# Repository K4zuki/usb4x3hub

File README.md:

# C92で購入いただいた方へ
- この本のPDFファイルは
  [こちら](https://github.com/K4zuki/usb4x3hub/releases/tag/c92-print-out)
- この本に登場する基板のデータは
  [こちら](https://github.com/K4zuki/usb4x3hub/releases/tag/r0.5-gerber-out)
- 秋月メモリ液晶基板の本は[こちら](https://github.com/K4zuki/AkiSpiLcd)です

# このリポジトリは何
コミケ９２に向けて書いていた本の原稿と、同時頒布を目指して設計を進めていた
基板の設計データです。原稿はmarkdownで書かれています。 設計データは
Eagle７系のbrdファイルとガーバデータです。

# USB4x3HUB: connects 4 USB hosts to share 3-port USB HUB
If you have **PCs, MACs, LINUXes, XBOXes and/or PS4s**, you can share your favorite Keyboard and Mouse (and one more)

> NOTE: I do not have PS4 so it is not tested;USB4x3HUB might not work with PS4

**rev 0.5 - みんなのラボ brand**

<!-- 
**rev 0.1** -->

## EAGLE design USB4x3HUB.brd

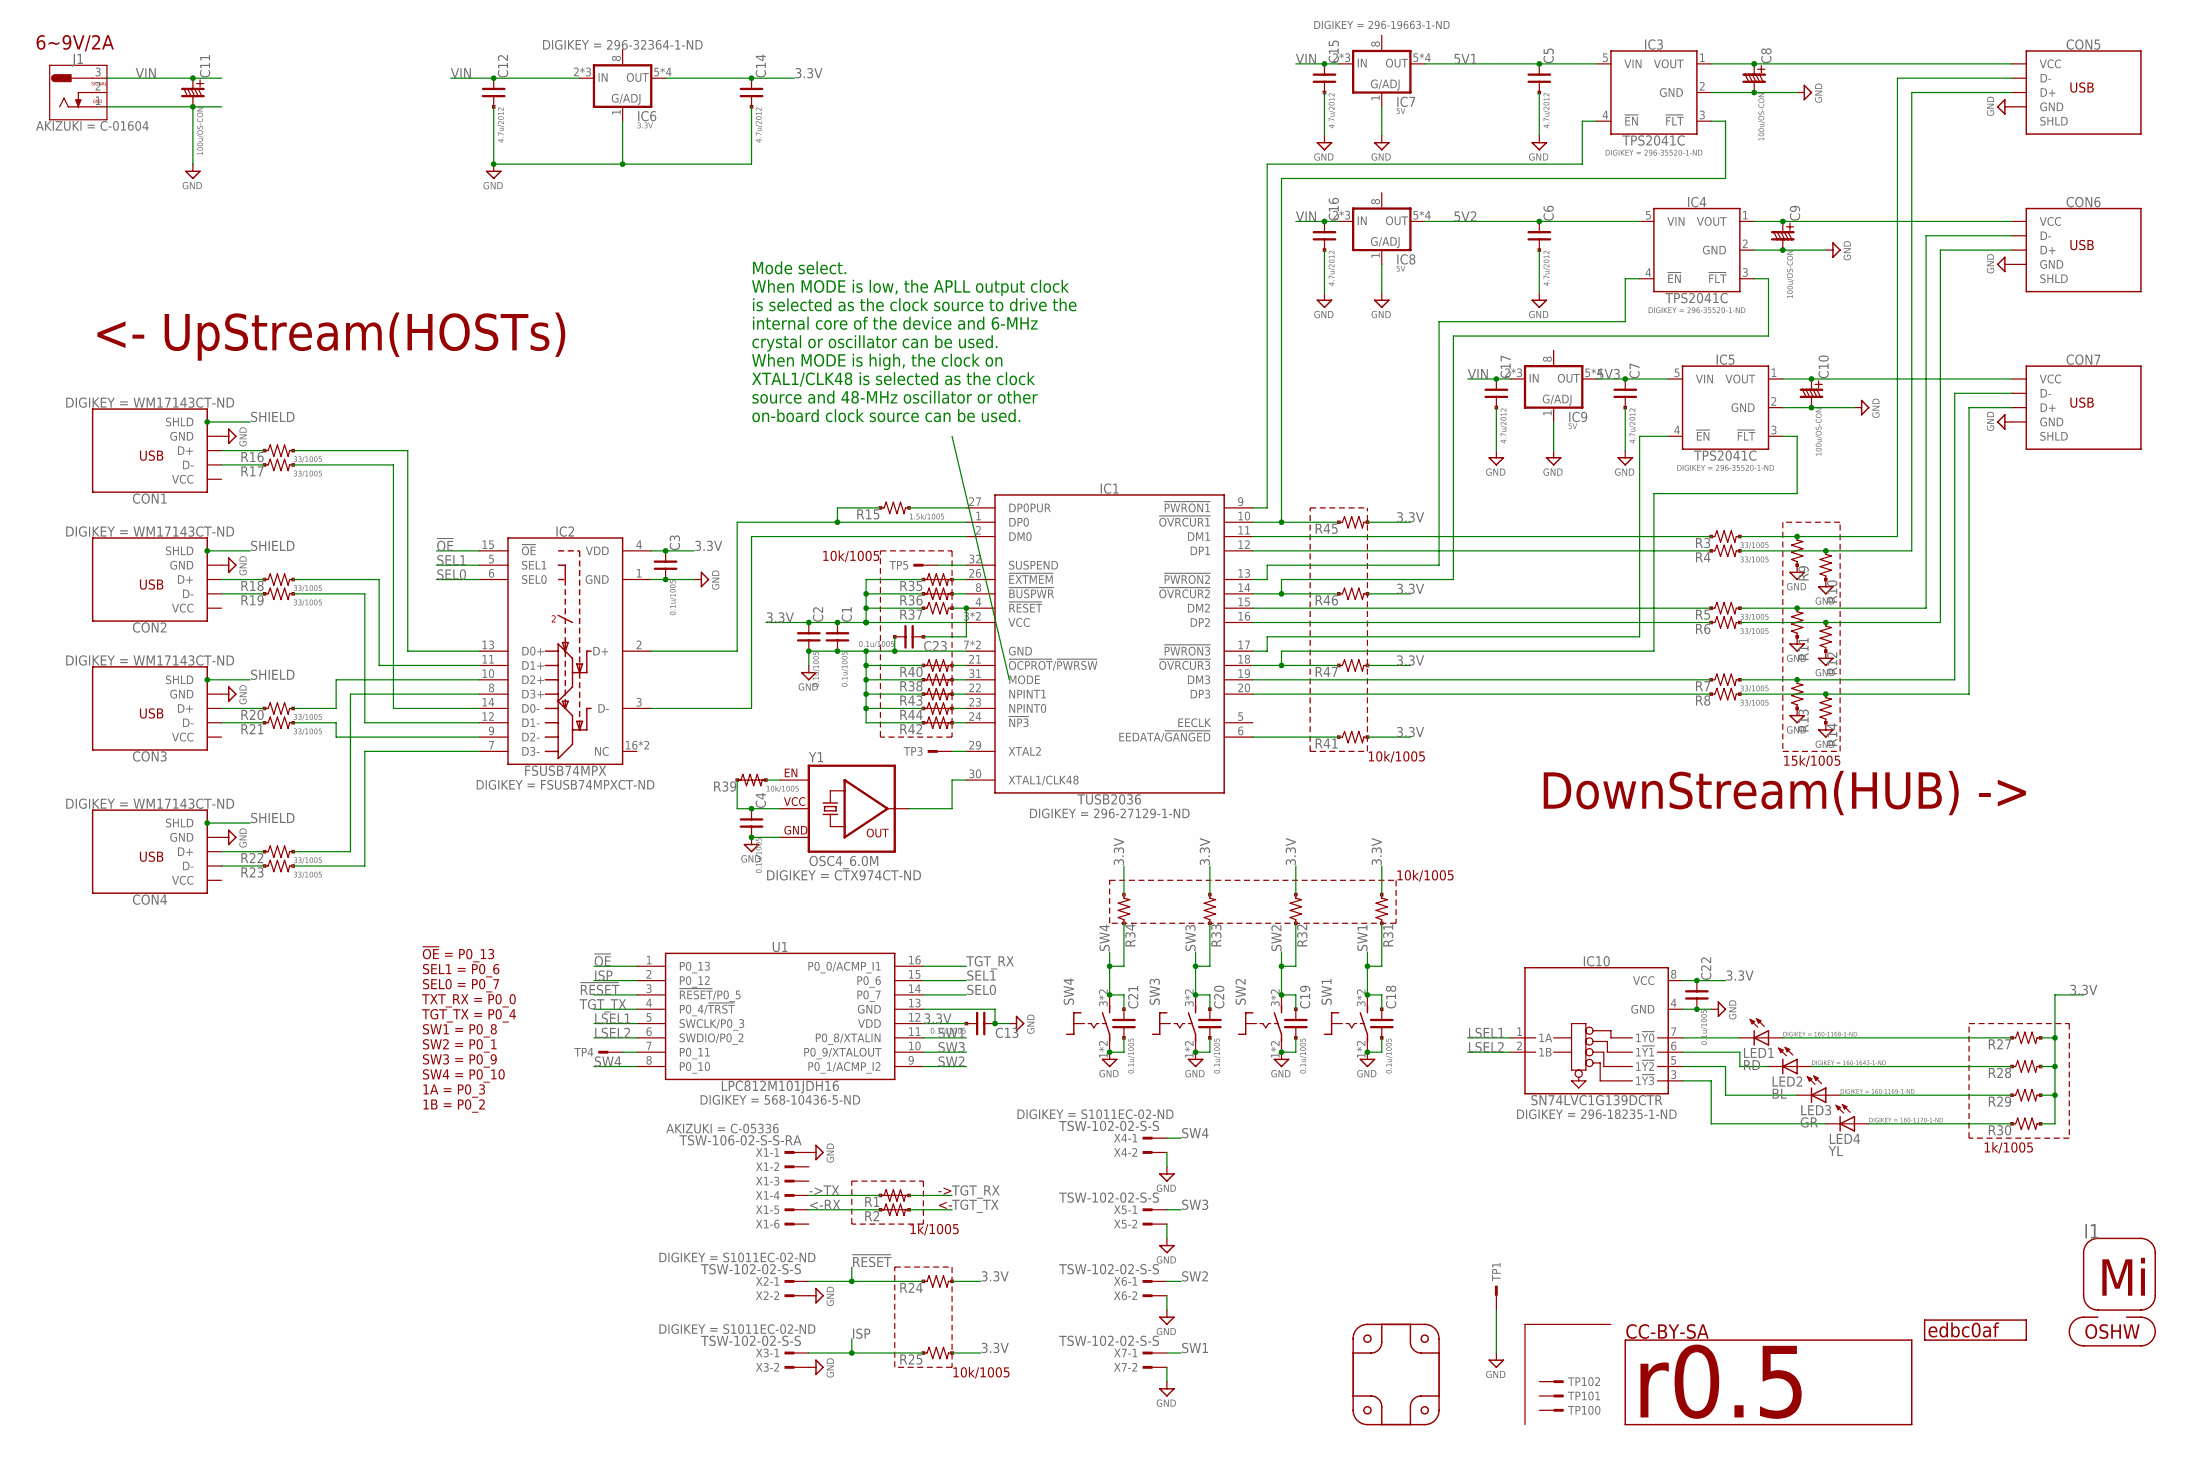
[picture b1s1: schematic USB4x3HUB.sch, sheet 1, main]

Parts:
C1, C2, C3, C4, C13, C18, C19, C20, C21, C22, C23: 0.1u/1005; C0402
C5, C6, C7, C12, C14, C15, C16, C17: 4.7u/2012; CR_2125
C8, C9, C10: 100u/OS-CON; C_2.5PHI5_875105142005WURTH
C11: 100u/OS-CON; C_2.5PHI6.3_C6
CON1, CON2, CON3, CON4: CON_USB_UB; CON_USB_47589-0001MOLEX
CON5, CON6, CON7: CON_USB_A_614104150121; CON_USB_614104150121WURTH
GIT1: edbc0af; GIT-REVISION
I1: ICON_MINLAB_5.2S; ICON_MINLAB_5.2MM
IC1: TUSB2036; QFP32_0.8P7.2X7.2
IC2: FSUSB74MPX; QFN16_0.5P3.0X3.0
IC3, IC4, IC5: TPS2041C; IC_05_0.95_50MIL
IC6: 3.3V; DFN80P410X410_8N
IC7, IC8, IC9: 5V; DFN80P410X410_8N
IC10: SN74LVC1G139DCTR; SOT65P315X290-8N
ICON1: OSHW; ICON_OSHW
ICON2: r0.5; ICON_REVISION2.0
J1: CON_DCJACK_C1604; CON_DCJACK_C-1604
LED1: RD; CHIPLED_0805
LED2: BL; CHIPLED_0805
LED3: GR; CHIPLED_0805
LED4: YL; CHIPLED_0805
P1, P2, P3, P4: PCB_CORNER
R1, R2, R35, R36, R38, R40, R42, R43, R44: R_US__1005SHORT; R0402SHORT
R3, R4, R5, R6, R7, R8, R16, R17, R18, R19, R20, R21, R22, R23: 33/1005; C0402
R9, R10, R11, R12, R13, R14: 15k/1005; C0402
R15: 1.5k/1005; C0402
R24, R25, R31, R32, R33, R34, R37, R41, R45, R46, R47: 10k/1005; C0402
R27, R28, R29, R30: 1k/1005; C0402
R39: 10k/1005; R0402SHORT
SW1, SW2, SW3, SW4: TACTSW2_WH_SKRPACE010; SW_TACTSW_SKRPACE010
TP1: TESTPAD_4020; TP_4020
TP3, TP4, TP5: TESTPAD; TP06RECT
TP100, TP101, TP102: TESTPAD_F; FIDUCIAL
U1: LPC812M101JDH16; SOT65P510X450X110-16N
X1: TSW-106-02-S-S-RA
X2, X3, X4, X5, X6, X7: TSW-102-02-S-S
Y1: OSC4_6.0M; CLOCK_2520

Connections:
3.3V: C1.1, C2.1, C3.1, C4.1, C13.2, C14.1, C22.1, IC1.3 (VCC), IC1.25 (VCC), IC2.4 (VDD), IC6.5 (OUT), IC6.6 (OUT), IC6.7 (OUT), IC6.EP (OUT), IC10.8 (VCC), R24.2, R25.2, R27.2, R28.2, R29.2, R30.2, R31.2, R32.2, R33.2, R34.2, R35.1, R35.2 (1), R36.1, R36.2 (1), R37.1, R39.1, R39.2 (1), R41.2, R45.2, R46.2, R47.2, U1.12 (VDD), Y1.4 (VCC)
5V1: C5.1, IC3.5 (VIN), IC7.5 (OUT), IC7.6 (OUT), IC7.7 (OUT), IC7.EP (OUT)
5V2: C6.1, IC4.5 (VIN), IC8.5 (OUT), IC8.6 (OUT), IC8.7 (OUT), IC8.EP (OUT)
5V3: C7.1, IC5.5 (VIN), IC9.5 (OUT), IC9.6 (OUT), IC9.7 (OUT), IC9.EP (OUT)
!OE!: IC2.15 (!OE!), U1.1 (P0_13)
!RESET!: R24.1, U1.3 (!RESET!/P0_5), X2.1
->TX: R1.1, R1.2 (1), X1.4
<-RX: R2.1, R2.2 (1), X1.5
GND: C1.2, C2.2, C3.2, C4.2, C5.2, C6.2, C7.2, C8.-, C9.-, C10.-, C11.-, C12.2, C13.1, C14.2, C15.2, C16.2, C17.2, C18.2, C19.2, C20.2, C21.2, C22.2, C23.2, CON1.5 (GND), CON2.5 (GND), CON3.5 (GND), CON4.5 (GND), CON5.4 (GND), CON6.4 (GND), CON7.4 (GND), IC1.7 (GND), IC1.28 (GND), IC2.1 (GND), IC3.2 (GND), IC4.2 (GND), IC5.2 (GND), IC6.1 (ADJ), IC7.1 (ADJ), IC8.1 (ADJ), IC9.1 (ADJ), IC10.4 (GND), J1.1 (3), R9.1, R10.1, R11.1, R12.1, R13.1, R14.1, R38.1, R38.2 (1), R40.1, R40.2 (1), R42.1, R42.2 (1), R43.1, R43.2 (1), R44.1, R44.2 (1), SW1.1, SW1.2, SW2.1, SW2.2, SW3.1, SW3.2, SW4.1, SW4.2, TP1.TP, U1.13 (GND), X1.1, X2.2, X3.2, X4.2, X5.2, X6.2, X7.2, Y1.2 (GND)
ISP: R25.1, U1.2 (P0_12), X3.1
LSEL1: IC10.1 (1A), U1.5 (SWCLK/P0_3)
LSEL2: IC10.2 (1B), U1.6 (SWDIO/P0_2)
unnamed: IC1.1 (DP0), IC2.2 (D+), R15.1
unnamed: IC1.2 (DM0), IC2.3 (D-)
unnamed: CON1.3 (D+), R16.1
unnamed: CON1.2 (D-), R17.1
unnamed: CON2.3 (D+), R18.1
unnamed: CON2.2 (D-), R19.1
unnamed: CON3.3 (D+), R20.1
unnamed: CON4.3 (D+), R22.1
unnamed: CON3.2 (D-), R21.1
unnamed: CON4.2 (D-), R23.1
unnamed: C8.+, CON5.1 (VCC), IC3.1 (VOUT)
unnamed: C9.+, CON6.1 (VCC), IC4.1 (VOUT)
unnamed: C10.+, CON7.1 (VCC), IC5.1 (VOUT)
unnamed: IC1.30 (XTAL1/CLK48), Y1.3 (OUT)
unnamed: IC1.10 (!OVRCUR1!), IC3.3 (!FLT!), R45.1
unnamed: IC1.9 (!PWRON1!), IC3.4 (!EN!)
unnamed: CON5.2 (D-), R3.2, R9.2
unnamed: CON5.3 (D+), R4.2, R10.2
unnamed: IC1.14 (!OVRCUR2!), IC4.3 (!FLT!), R46.1
unnamed: IC1.13 (!PWRON2!), IC4.4 (!EN!)
unnamed: CON6.2 (D-), R5.2, R11.2
unnamed: CON6.3 (D+), R6.2, R12.2
unnamed: IC1.17 (!PWRON3!), IC5.4 (!EN!)
unnamed: IC1.18 (!OVRCUR3!), IC5.3 (!FLT!), R47.1
unnamed: CON7.2 (D-), R7.2, R13.2
unnamed: CON7.3 (D+), R8.2, R14.2
unnamed: IC1.6 (EEDATA/!GANGED!), R41.1
unnamed: IC1.11 (DM1), R3.1
unnamed: IC1.12 (DP1), R4.1
unnamed: IC1.15 (DM2), R5.1
unnamed: IC1.16 (DP2), R6.1
unnamed: IC1.19 (DM3), R7.1
unnamed: IC1.20 (DP3), R8.1
unnamed: IC1.27 (DP0PUR), R15.2
unnamed: IC2.13 (D0+), R16.2
unnamed: IC2.11 (D1+), R18.2
unnamed: IC2.10 (D2+), R20.2
unnamed: IC2.8 (D3+), R22.2
unnamed: IC2.14 (D0-), R17.2
unnamed: IC2.12 (D1-), R19.2
unnamed: IC2.9 (D2-), R21.2
unnamed: IC2.7 (D3-), R23.2
unnamed: IC1.32 (SUSPEND), TP5.TP
unnamed: IC10.7 (1!Y0!), LED1.C
unnamed: IC10.6 (1!Y1!), LED2.C
unnamed: IC10.5 (1!Y2!), LED3.C
unnamed: IC10.3 (1!Y3!), LED4.C
unnamed: LED4.A, R30.1
unnamed: LED3.A, R29.1
unnamed: LED2.A, R28.1
unnamed: LED1.A, R27.1
unnamed: IC1.29 (XTAL2), TP3.TP
unnamed: IC1.26 (!EXTMEM!), R35.3 (2)
unnamed: IC1.8 (!BUSPWR!), R36.3 (2)
unnamed: C23.1, IC1.4 (!RESET!), R37.2
unnamed: IC1.21 (!OCPROT!/!PWRSW!), R40.3 (2)
unnamed: IC1.31 (MODE), R38.3 (2)
unnamed: IC1.22 (NPINT1), R43.3 (2)
unnamed: IC1.23 (NPINT0), R44.3 (2)
unnamed: IC1.24 (!NP3!), R42.3 (2)
unnamed: R39.3 (2), Y1.1 (C)
unnamed: TP4.TP, U1.7 (P0_11)
SEL0: IC2.6 (SEL0), U1.14 (P0_7)
SEL1: IC2.5 (SEL1), U1.15 (P0_6)
SHIELD: CON1.SHD (SHLD), CON1.SHD$1 (SHLD), CON1.SHD$2 (SHLD), CON1.SHD$3 (SHLD), CON1.SHD$4 (SHLD), CON1.SHD$5 (SHLD), CON1.SHD$6 (SHLD), CON1.SHD$7 (SHLD), CON2.SHD (SHLD), CON2.SHD$1 (SHLD), CON2.SHD$2 (SHLD), CON2.SHD$3 (SHLD), CON2.SHD$4 (SHLD), CON2.SHD$5 (SHLD), CON2.SHD$6 (SHLD), CON2.SHD$7 (SHLD), CON3.SHD (SHLD), CON3.SHD$1 (SHLD), CON3.SHD$2 (SHLD), CON3.SHD$3 (SHLD), CON3.SHD$4 (SHLD), CON3.SHD$5 (SHLD), CON3.SHD$6 (SHLD), CON3.SHD$7 (SHLD), CON4.SHD (SHLD), CON4.SHD$1 (SHLD), CON4.SHD$2 (SHLD), CON4.SHD$3 (SHLD), CON4.SHD$4 (SHLD), CON4.SHD$5 (SHLD), CON4.SHD$6 (SHLD), CON4.SHD$7 (SHLD)
SW1: C18.1, R31.1, SW1.3 (S), SW1.4 (S), U1.11 (P0_8/XTALIN), X7.1
SW2: C19.1, R32.1, SW2.3 (S), SW2.4 (S), U1.9 (P0_1/ACMP_I2), X6.1
SW3: C20.1, R33.1, SW3.3 (S), SW3.4 (S), U1.10 (P0_9/XTALOUT), X5.1
SW4: C21.1, R34.1, SW4.3 (S), SW4.4 (S), U1.8 (P0_10), X4.1
TGT_RX: R1.3 (2), U1.16 (P0_0/ACMP_I1)
TGT_TX: R2.3 (2), U1.4 (P0_4/!TRST!)
VCC: CON4.1 (VCC)
VIN: C11.+, C12.1, C15.1, C16.1, C17.1, IC6.2 (IN), IC6.3 (IN), IC6.4 (IN), IC7.2 (IN), IC7.3 (IN), IC7.4 (IN), IC8.2 (IN), IC8.3 (IN), IC8.4 (IN), IC9.2 (IN), IC9.3 (IN), IC9.4 (IN), J1.3 (1)

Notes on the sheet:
!OE! = P0_13 SEL1 = P0_6 SEL0 = P0_7 TXT_RX = P0_0 TGT_TX = P0_4 SW1 = P0_8 SW2 = P0_1 SW3 = P0_9 SW4 = P0_10 1A = P0_3 1B = P0_2
<- UpStream(HOSTs)
DownStream(HUB) ->
CC-BY-SA
15k/1005
1k/1005
10k/1005
6~9V/2A
Mode select. When MODE is low, the APLL output clock is selected as the clock source to drive the internal core of the device and 6-MHz crystal or oscillator can be used. When MODE is high, the clock on XTAL1/CLK48 is selected as the clock source and 48-MHz oscillator or other on-board clock source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

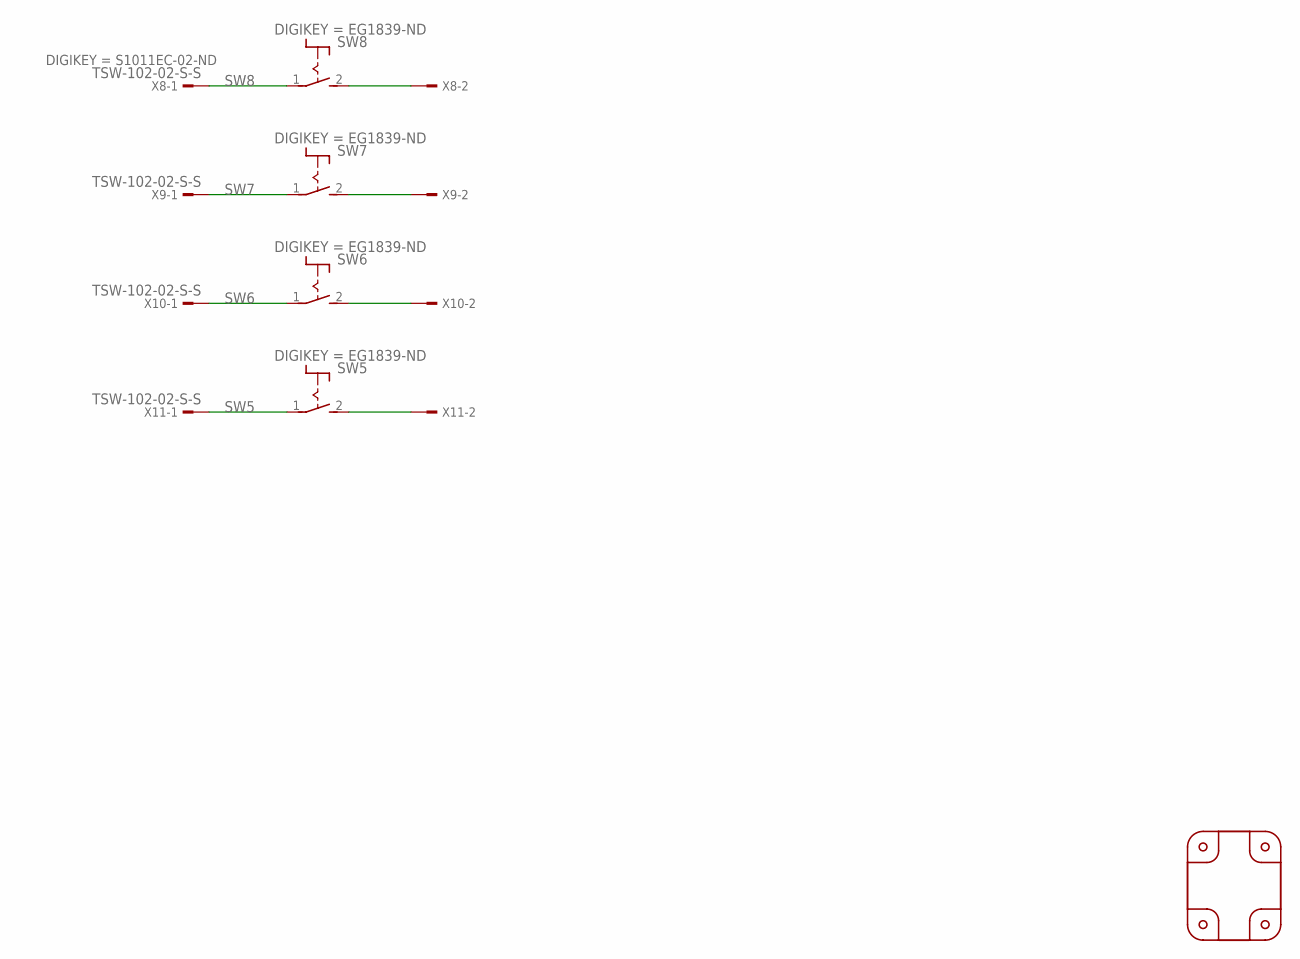
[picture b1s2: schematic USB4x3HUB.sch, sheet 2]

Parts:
P5, P6: PCB_CORNER
P7, P8: PCB_CORNER_NH
SW5, SW6, SW7, SW8: TACTSW2_BK_TL1105S; SW_TACTSW_TL1105S
X8, X9, X10, X11: TSW-102-02-S-S

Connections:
unnamed: SW8.2 (S), X8.2
unnamed: SW7.2 (S), X9.2
unnamed: SW6.2 (S), X10.2
unnamed: SW5.2 (S), X11.2
SW5: SW5.1, X11.1
SW6: SW6.1, X10.1
SW7: SW7.1, X9.1
SW8: SW8.1, X8.1

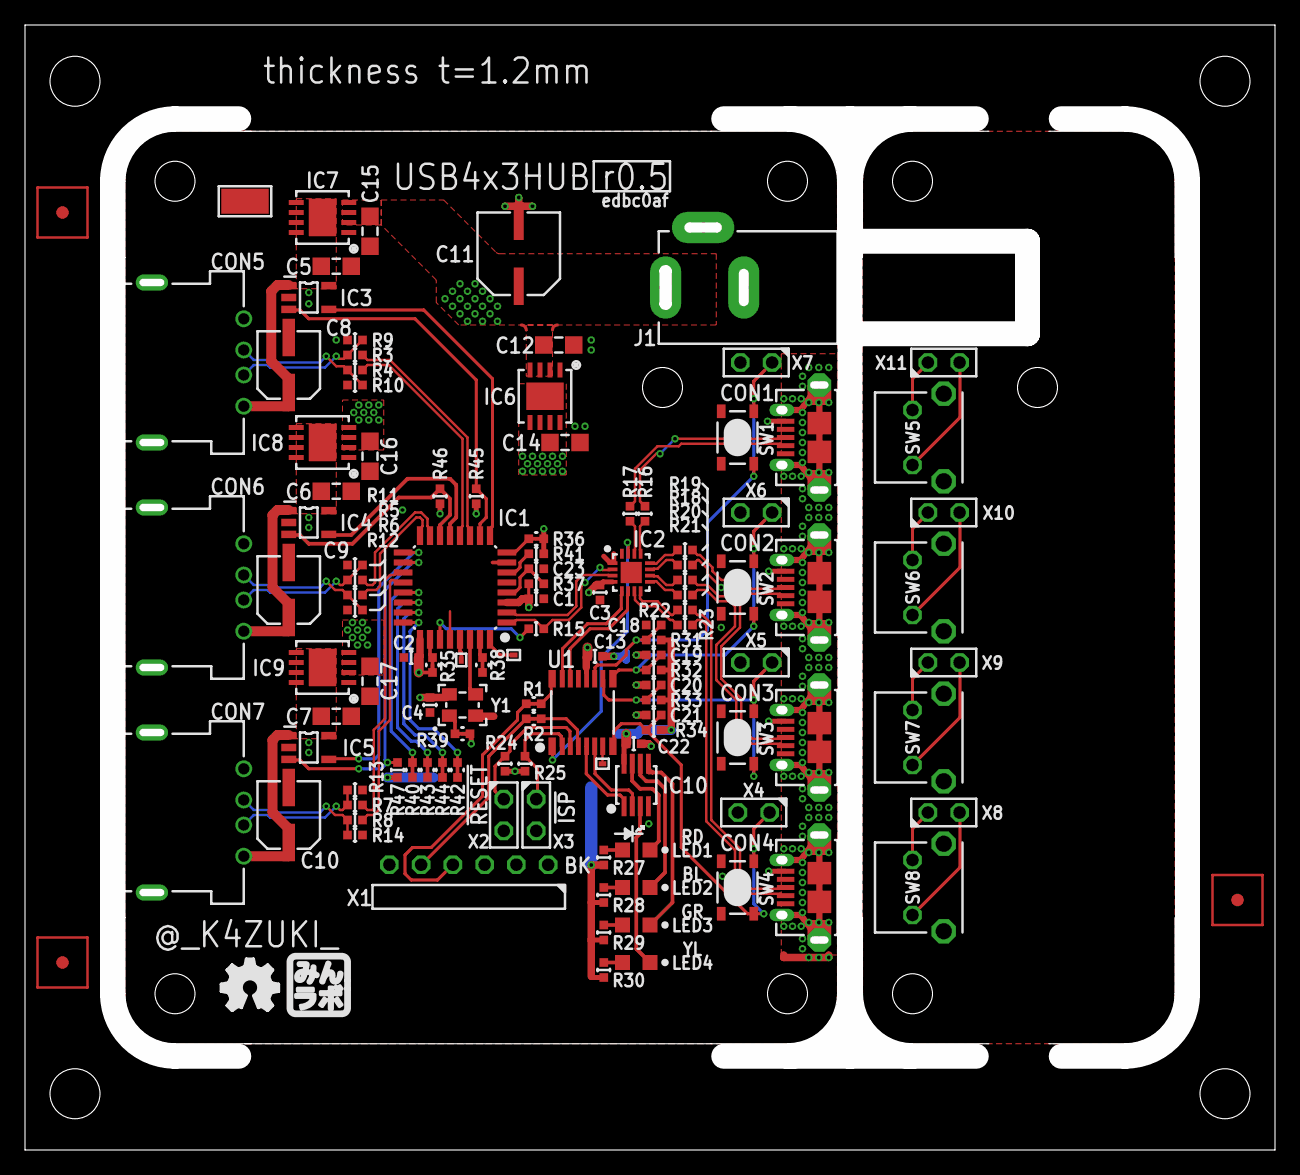
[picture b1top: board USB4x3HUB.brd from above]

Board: 2 copper layers, 98.0 x 88.0 mm, 131 parts (0 on the bottom side), 92 nets.

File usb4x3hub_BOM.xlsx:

Qty | Value | Device | Package | Parts | Description | AKIZUKI | DIGIKEY | MOUSER | NOT_COMPONENT | SEEED | SMD_PAD | TH_PAD | SMD_TOTAL | TH_TOTAL
1 |  | TESTPAD_4020 | TP_4020 | TP1 | test points |  | 36-5019CT-ND |  |  |  | 1 |  | 1 | 0
4 |  | CON_USB_UB | CON_USB_47589-0001MOLEX | CON1, CON2, CON3, CON4 | USB B CONNECTOR |  | WM17143CT-ND |  |  |  | 11 |  | 44 | 0
1 | LPC812M101JDH16 | IC_LPC81X_16_JDH16 | SOT65P510X450X110-16N | U1 | LPC81X microcontroller |  | 568-10436-5-ND |  |  |  | 16 |  | 16 | 0
1 | FSUSB74MPX | IC_USB_FSUSB74 | QFN16_0.5P3.0X3.0 | IC2 | 4 to 1 USB switch |  | FSUSB74MPXCT-ND |  |  |  | 17 |  | 17 | 0
11 | 0.1u/1005 | C_SMD_0.1U_1005 | C0402 | C1, C2, C3, C4, C13, C18, C19, C20, C21, C22, C23 | SMD CAPACITOR |  | 490-3261-1-ND |  |  | 302010024 | 2 |  | 22 | 0
1 | 1.5k/1005 | R_US_1.5K_1005 | C0402 | R15 | SMD resistor |  | P1.50KLCT-ND |  |  | 301010001 | 2 |  | 2 | 0
1 | 100u/OS-CON | C_DENKAI_100U_2.5P6.3_C6 | C_2.5PHI6.3_C6 | C11 | Chemical capacitor |  | P16468CT-ND |  |  |  | 2 |  | 2 | 0
3 | 100u/OS-CON | C_DENKAI_100U_875105142005WURTH | C_2.5PHI5_875105142005WURTH | C8, C9, C10 | Chemical capacitor |  | 732-6394-1-ND |  |  |  | 2 |  | 6 | 0
11 | 10k/1005 | R_US_10K_1005 | C0402 | R24, R25, R31, R32, R33, R34, R37, R41, R45, R46, R47 | SMD resistor |  | P10.0KLCT-ND |  |  | 301010047 | 2 |  | 22 | 0
6 | 15k/1005 | R_US_15K_1005 | C0402 | R9, R10, R11, R12, R13, R14 | SMD resistor |  | P15.0KLCT-ND |  |  | 301010042 | 2 |  | 12 | 0
4 | 1k/1005 | R_US_1.0K_1005 | C0402 | R27, R28, R29, R30 | SMD resistor |  | P1.00KLCT-ND |  |  | 301010006 | 2 |  | 8 | 0
14 | 33/1005 | R_US_33R_1005 | C0402 | R3, R4, R5, R6, R7, R8, R16, R17, R18, R19, R20, R21, R22, R23 | SMD resistor |  | P33.0LCT-ND |  |  | 301010609 | 2 |  | 28 | 0
8 | 4.7u/2012 | C_SMD_4.7U_2012 | CR_2125 | C5, C6, C7, C12, C14, C15, C16, C17 | SMD CAPACITOR |  | 490-9962-1-ND |  |  |  | 2 |  | 16 | 0
1 | BL | LEDBLCHIPLED_0805 | CHIPLED_0805 | LED2 | LED | I-06424 | 160-1643-1-ND |  |  | 304090061 | 2 |  | 2 | 0
1 | BL | TACTSW2_FSM2JMTR | SW_TACTSW_FSM2JMTR | SW2 | 2P tact switch |  | 450-2146-1-ND |  |  |  | 2 |  | 2 | 0
1 | GR | LEDGRCHIPLED_0805 | CHIPLED_0805 | LED3 | LED | I-06423 | 160-1169-1-ND |  |  | 304090057 | 2 |  | 2 | 0
1 | GR | TACTSW2_FSM2JMTR | SW_TACTSW_FSM2JMTR | SW3 | 2P tact switch |  | 450-2146-1-ND |  |  |  | 2 |  | 2 | 0
1 | RD | LEDRDCHIPLED_0805 | CHIPLED_0805 | LED1 | LED | I-06419 | 160-1168-1-ND |  |  | 304090046 | 2 |  | 2 | 0
1 | RD | TACTSW2_FSM2JMTR | SW_TACTSW_FSM2JMTR | SW1 | 2P tact switch |  | 450-2146-1-ND |  |  |  | 2 |  | 2 | 0
1 | YL | LEDYLCHIPLED_0805 | CHIPLED_0805 | LED4 | LED | I-06420 | 160-1170-1-ND |  |  | 304090039 | 2 |  | 2 | 0
1 | YL | TACTSW2_FSM2JMTR | SW_TACTSW_FSM2JMTR | SW4 | 2P tact switch |  | 450-2146-1-ND |  |  |  | 2 |  | 2 | 0
1 | TUSB2036 | IC_USB_TUSB2036 | QFP32_0.8P7.2X7.2 | IC1 | 2/3-port USB hub IC |  | 296-27129-1-ND |  |  |  | 32 |  | 32 | 0
1 | OSC4_6.0M | OSC4_6.0M | CLOCK_2520 | Q1 |  |  | CTX974CT-ND |  |  |  | 4 |  | 4 | 0
3 | TPS2041C | IC_POWER_TPS2041C | IC_05_0.95_50MIL | IC3, IC4, IC5 | power switch |  | 296-35520-1-ND |  |  |  | 5 |  | 15 | 0
1 | SN74LVC1G139DCTR | IC_TTL_SINGLE_74_139_FLAT | SOT65P315X290-8N | IC10 | single 74 logic IC: 139 |  | 296-18235-1-ND |  |  |  | 8 |  | 8 | 0
1 | 3.3V | LDO4_3.3_DRJ | DFN80P410X410_8N | IC6 | LDO with 4 pins |  | 296-32364-1-ND |  |  |  | 9 |  | 9 | 0
3 | 5V | LDO4_5.0_DRJ | DFN80P410X410_8N | IC7, IC8, IC9 | LDO with 4 pins |  | 296-19663-1-ND | 595-TLV1117-50CDRJR |  |  | 9 |  | 27 | 0
1 |  | CON_DCJACK_C1604 | CON_DCJACK_C-1604 | J1 | DC JACK : 2.1 / 2.5 mm | C-01604 |  | 163-179PH-EX |  | 320120003 |  | 3 | 0 | 3
3 |  | CON_USB_A_614104150121 | CON_USB_614104150121WURTH | CON5, CON6, CON7 | USB B CONNECTOR |  | 732-5962-1-ND | 710-614104150121 |  |  |  | 6 | 0 | 18
1 | TSW-106-02-S-S-RA | TSW-106-02-S-S-RA | TSW-106-02-S-S-RA | X1 | THROUGH-HOLE HEADER | C-05336 | 952-2372-ND |  |  | 320020019 |  | 6 | 0 | 6
2 | TSW-102-02-S-S | TSW-102-02-S-S | TSW-102-02-S-S | X2, X3 | THROUGH-HOLE POST HEADER |  | S1011EC-02-ND |  | YES | 320020016 |  | 2 | 0 | 4
1 |  | ICON_MINLAB_5.2S | ICON_MINLAB_5.2MM | I1 |  |  |  |  | YES |  |  |  | 307 | 31
4 |  | PCB_CORNER | PCB_CORNER | P1, P2, P3, P4 |  |  |  |  | YES
9 |  | R_US__1005SHORT | R0402SHORT | R1, R2, R35, R36, R38, R40, R42, R43, R44 | SMD resistor |  |  |  | YES
3 |  | TESTPAD | TP06RECT | TP3, TP4, TP5 | test points |  |  |  | YES
3 |  | TESTPAD_F | FIDUCIAL | TP100, TP101, TP102 | test points |  |  |  | YES
1 | 10k/1005 | R_US__1005SHORT | R0402SHORT | R39 | SMD resistor |  |  |  | YES
1 | 7236034 | GIT-REVISION_1.0 | GIT-REVISION | GIT1 |  |  |  |  | YES
1 | OSHW | ICON_OSHW | ICON_OSHW | ICON1 | Silk icon of OSHW |  |  |  | YES
1 | r0.5 | ICON_REVISION_2.0 | ICON_REVISION2.0 | ICON2 |  |  |  |  | YES

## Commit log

2015-10-28 first commit .gitignore USB4x3HUB.brd/sch
2015-10-28 [ NEW ] USB4x3HUB.png
2015-10-28 rename png; update README
2015-10-30 [ NEW ] USB4x3HUB.md
    BOM table
2015-10-30 BOM fix
2015-10-30 update BOM table
2015-10-30 [ FIX ] add 5V LDO on each device ports; switches moved to each host ports
2015-10-31 [ NEW ] r0.1releasenote.md
2015-10-31 rename USB4x3HUB.png to USB4x3HUBr1.png
2015-10-31 BOM list for r1 schematic
2015-10-31 md's update correct revision number fix to point correct pic
2015-10-31 [ FIX ] correct some setting-pin connection
2015-11-04 [ r0.1 ] BOM update
2015-11-05 [ r0.1 ] combined BOM
2015-11-05 [ r0.2 ] update to reflect library update
2015-11-06 [ r0.1 ] documents update
2015-11-06 README fix
2015-11-07 README update
2015-11-07 [ r0.1 ] BOM modified to separate AKIZUKI and DigiKey
2015-11-07 [r0.2] add LEDs, add single logic 139, modify CON1-4, move silk
2015-11-07 [r0.2] LED1-4/R27-30 silk
2015-11-09 [ r0.1 ] release note update
2015-11-09 [ NEW ] mbed (Mercurial) repository: usb4x3hub
2015-11-09 [r0.2] library update
2015-11-14 [ r0.2 ] library update;Q1 replace;IC2 move East
2015-11-16 [ r0.2 ] tCream update by library
2015-11-16 [ r0.2 ][ NEW ] R35-37; tCream update; CON5-7 move; C8-10/14-16 replace size
2015-11-26 update eagle version = 7.5.0; library update
2015-12-01 library update: R_US_*
2015-12-21 [ r0.3 ] move IC1 and surroundings; replace U1 to use TSSOP(JDH16); ICON_REVISION
2015-12-22 [ r0.3 ] update BOM; fix HUB BUS line
2015-12-24 [ r0.3 ] library update
2015-12-24 [ r0.3 ] add placement coordinate list
2015-12-29 [ NEW ] USB4x3HUB.csv: a BOM file
2015-12-29 [ NEW ] Geber files and gerbv project file
2015-12-29 ignore lock files
2015-12-29 [ r0.3 ] change NAME labels alignment to center; fix UART pins P0_0 and P0_4 must be used for UART as they are used by ISP
2016-01-06 Revision 0.3
2016-01-08 library update: CON1-4 milling and IC10 attribute
2016-01-29 [ NEW ] r0.3 release note detail of PCB itself and known issue(s)
2016-02-04 replace Q1 to use Oscillator add R39~45; add TP3; remove C21
2016-02-04 library update; add DIGIKEY attributes
2016-02-06 add C21-5,TP4,R45-7;move R16-23;OE=P0_13;add silk to point color for SW1-4
2016-02-06 move some wire: library update
2016-02-06 replace IC6-9 *CAUTION: airwires remain*
2016-02-07 C11: library update, C5-7 moved
2016-02-07 C8-11 replaced by OS-CON 16V/100uF; PCB width shrinked 10mm(and necessary moves)
2016-02-07 move mbed souce and library to mbed/
2016-02-09 Capacitors renumbered
2016-02-09 some trace width wider 0.2 -> 0.25mm; Capacotors re-numbering
2016-02-13 IC6/R16-23,31-34,36,37,41/C1,12,14,18-23 move; LED1-4 colors
2016-02-13 [ NEW ] USB4x3HUB r0.4 BOM table
2016-02-13 library update; MinLab brand;R15
2016-02-13 move USB4x3HUBr1.png to doc/
2016-02-13 [ NEW ] r04 PCB pic
2016-02-16 library update; PCB width shrink 2.5mm and related moves
2016-02-16 Description update
2016-02-16 library update
2016-02-17 library update; panel design example in dxf layer
    MXA2-8-6SS panel marutsu.co.jp/pc/i/136286/
2016-02-17 library update; [ NEW ] TB111-2-2-U-1-1 for J1 alternate
2016-02-17 tRestrict
2016-02-17 X1-3,R1/2 move north; J2 move - related move
2016-02-17 dxf layer
2016-02-17 JUST in MXA2-8-6SS (TAKACHI)
2016-02-18 [ r0.4 ] sch w/ sha1sum
2016-02-18 silk; README
2016-02-27 replace C8-10; replace CON5-7;move R27-30;move LED colors library update
2016-03-05 library update; some1Ks,10Ks to use default-shorted resistors
2016-03-07 SW1-4 replace to SMD package
2016-03-07 R1/2/24/25 move
2016-03-08 move md/csv/png to doc/
2016-06-25 BOM change
2016-06-25 git revision
2016-06-25 sorted
2016-06-27 quotations
2016-06-27 Gerber r0.4-a30fd1f
2016-06-27 [ r0.4 ] Pic update
2016-06-27 typo
2016-09-15 [ NEW ] add book publish set; ignore make-* outputs
2016-09-16 [ DOC ] revision is 1.0
2016-10-31 [ DOC ] update Makefile; TITLE.md for abstract of document
    - update Makefile to apply recent update in pandoc_misc
    - update TITLE.md to add abstracet of document
2016-10-31 [ DOC ] fix Makefile
2016-11-15 [ DOC ] fix abstract; add 1st chapter
2016-11-16 [ DOC ] fix Makefile to add prefix directory $(MDDIR)/
2016-11-16 [ DOC ] move doc/*.png PNG image files to doc/images
2016-11-16 [ DOC ] fix Makefile; add image links
    [ TODO ] make-html and make-pdf behaves different about image inports
2016-11-16 [ DOC ] add dimention image picture with rotation feature
2016-11-18 [ DOC ] only make-{all, html, pdf, clean} implemented in top Makefile
    - Makefile/Makefile.in in project root decreased function
    - add doc/Makefile{,.in} to do actual make-* commands
2016-11-18 fix stupid missing backslash
2016-11-18 [ DOC ] add microcontroller zoomed schematic image; mbed code formatted
    - add doc/images/USB4x3HUB_r04_LPC812.png
    - apply clang-format on mbed/main.cpp
    - add listingtable of mbed/main.cpp
2016-11-21 top Makefile calls doc/Makefile; fix doc/Makefile for tex/pdf output
2016-11-23 [ DOC ] add enclosure part list table
2016-11-23 [ PCB ] prepare for panel consideration
2016-11-28 [ DOC ] add case2.csv
2016-11-28 [ DOC ] fix TITLE.md and case1.csv
2016-12-03 [ DOC ] fix case2.csv table contents; fix instructions for 2nd enclosure idea
    TODO: primary enclosure idea requires reconsideration on panel design
2016-12-06 library update; IC10 value updated/corrected
    - IC10 = SN74LVC1G139DCTR(was: SN74LVC1G139DCUR)
2016-12-06 update library
2016-12-08 a layer change from Dimention to Measures
2016-12-16 [ BRD ] panel design reconsideration
2016-12-17 [ BRD ] measures
2016-12-17 [ PCB ] library update
2016-12-17 [ PCB ] apply library update
2016-12-21 [ DOC ] make-clean cleans rotated images also
2016-12-21 [ DOC ] one TODO down; one TODO added
2016-12-21 [ DOC ] update (rotated) images
2016-12-21 correct enclosure part number
2016-12-24 [ DOC ] add `\newpage` after board image(Appendix)
2016-12-24 [ DOC ] add note after demention data
2016-12-24 [ DOC ] C91 board did not make it
2016-12-24 remove eagle.epf from version control and added to ignore list
2016-12-24 remove debug.log; ignore *.log
2016-12-24 [ DOC ] add another table to list additional components
2016-12-24 fix added table
2016-12-24 [ PCB ][ SCH ] attribute font change; attribute position change
2016-12-24 [ MBED ] remove comments
2016-12-24 [ DOC ] fixes; add tailnotes
2016-12-24 [ PCB ][ SCH ] fix attributes
2016-12-25 [ DOC ] tailnote is revision history
2016-12-25 [ DOC ] section title; typo; disclaimer
2016-12-28 fix README for C91 publish
2017-01-01 [ BRD ] library update; panel design update
2017-01-31 [ PCB ] start r0.5 develop
    - remove GND terminal(TP1)
    - move switches and microB to south
    - some silk move regards to this
    - move DC jack to face on microB side
    - future: microB move to bottom side, and replace switch to panel type?
2017-02-01 [ PCB ] move panel switch holes south by 1mm
2017-02-01 [ PCB ] library update and related fix
    - CON5-7 pinout mistake fixed in library
    - move C8-10 to followw this change
2017-02-05 [ PCB ] move C8-10; shift USB downstream traces
2017-02-19 [ BRD ] fix clock mode
    - 48M source used while 6M source selected for IC
2017-02-19 apply library updates; regenerate BOM
    - add SMD_PAD/TH_PAD attributes
    - update some supplier attributes
    - update BOM based on this update
2017-02-20 [ BRD ] board width is 57.0mm
2017-02-21 [BRD] replace SW1-4;add pin headers for daughter board
2017-02-22 [ BRD ] X4-7 pin1 connects to each switch inputs
    - move SW1-4 silk
    - move CON1-4 silk
    - move X4-7 silk
    - add 2.8mm hole for M2.6 screw
    - add tRestrict zone for it
2017-02-22 [ BRD ] clean ratsnest
2017-02-22 [ PCB ] add sheet for daughter board; move M2.6 hole; library update
    - prepare daughter board
    - apply updated library and use TACTSW2 component
    - more consideration required
2017-02-22 [ PCB ] update library; remove south M2.6 hole; update panel design to reflect design change
2017-02-27 [ PCB ] library update etc.
    - SW assy on top
    - make room for DC jack
2017-02-27 [ SCH ] Q1 replaced to 6M clock
2017-02-27 [ BRD ] increase room for DC jack; use M3 instead of M2.6
    - I have quite many M3 spacers
2017-02-27 [ BRD ] update panel design
    - DC jack height is 11mm instead of 10mm
2017-02-27 Set theme jekyll-theme-minimal
2017-02-27 README: update link to r0.4 release page
    - apply tag change
2017-02-28 [ DOC ] updates for document
2017-03-04 [ DOC ] update doc and BOM
2017-03-29 [ DOC ] add front page image and source images/pptx
    - http://www.irasutoya.com/
2017-03-31 [ DOC ] update README and tailnote
2017-04-05 [ DOC ] update front page image
2017-04-13 update README
    - mentions 技術書典２
2017-04-16 update ppt
2017-07-31 update panel width; fix DRC ererror
2017-07-31 update Makefile
2017-07-31 r0.5 gerber out
2017-07-31 update doc
    - replace listingtable by new syntax
    - update table importers to use direct table in code block
2017-08-01 update Makefile-s
    - root/Makefile:
    - remove comments
    - add $(MAKE) variable to switch make command
    - doc/Makefile:
    - defines only minimum set of global variable
    - defines project specific variables
2017-08-01 table block updated
    external csv includesion fails on windows
2017-08-01 update title and tailnote
2017-08-01 additionally needs to change from default
2017-08-01 add r0.5 images
2017-08-01 ignore references/
2017-08-01 updates by replacing inline table and image rotating
2017-08-07 library update; rename Q1 to Y1
2017-08-07 update tables
2017-08-08 update BOM
2017-08-08 add section to include updated BOM
2017-08-08 rename BOM table and moved into data directory
2017-08-08 explain difference from previous revision
2017-08-08 2nd enclosure idea is back
    - update revision difference
    - update tailnote()
2017-08-08 update tailnote
2017-08-08 add an image
2017-08-08 update milling and drill
    - replace by 2.8mm drill hole
    - for M2.6 spacer
    - extend DC jack milling
2017-08-08 sub board has corner holes on connector side
    - add shield vias
    - back to 3.2mm hole
2017-08-08 add footnote
2017-08-08 add section to mention ika_shouyu_poppoyaki
2017-08-08 edit image
2017-08-20 Update README.md
    fix link to PDF file
2017-08-20 [DOC] Makefile.in no longer used
2017-08-20 yaml header moved to config.yaml
2017-08-20 [ DOC ] TITLE.md moved to markdown/
2017-08-20 update doc/Makedile
2019-08-14 ignore Out/ directory contents
